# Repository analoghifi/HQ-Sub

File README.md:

# HQ-Sub  
adjustable\* 5th order (**30 dB/oct.**) subsonic filter  
mono module  
\*(13-53Hz / in 2-3Hz steps / 16 steps)  
  
https://web.archive.org/web/20160324051200/http://thel-audioworld.de/module/Filterzone/HQ-Sub.htm

----  

----  

### Frequency Table:  
* 0: 13Hz
* 1: 15Hz
* 2: 18Hz
* 3: 21Hz
* 4: 23Hz
* 5: 26Hz
* 6: 29Hz
* 7: 31Hz
* 8: 34Hz
* 9: 36Hz
* A: 39Hz
* B: 41Hz
* C: 44Hz
* D: 47Hz
* E: 50Hz
* F: 53Hz  

All 5 switches must always be in the same position (!)  
  
----  
  
### A note on the capacitors used in the original design  
The basic problem is:  
to get meaningful (= not too high) resistance values in this 5th order filter design we want to use 1µF capacitors.  
However, 1µF capacitors are generally not available in the KP film/foil version,  
at least not with a 1% tolerance and/or in suitable small dimensions for this small PCB.  
  
regarding C8-C17 in the original design:  
the 1µF MKS capacitors are paralleled with 22nF KP capacitors  
to compensate the very bad (=very high) dissipation factor (tanδ) of the MKS capacitors  
originally equipped with:  
WIMA MKS4    1µF/63V 10%   (Metallized Polyester (PET))     tanδ=8x10<sup>-3</sup> -> <a href="https://github.com/analoghifi/capacitors/blob/main/audio%20and%20filter%20capacitors/docs/datasheets/dont%20use/PET%20MKS/WIMA_MKS_4__EN.pdf">Datasheet</a>  
WIMA FKP2  0,022µF/63V 5%  (film/foil Polypropylene) tanδ=5x10<sup>-4</sup> -> <a href="https://github.com/analoghifi/capacitors/blob/main/audio%20and%20filter%20capacitors/docs/datasheets/kp/WIMA_FKP_2__NEW_ROHS__EN.pdf">Datasheet (ROHS-version)</a>  
(better old FKP2 version "NOS" without ROHS -> <a href ="https://github.com/analoghifi/capacitors/blob/main/audio%20and%20filter%20capacitors/docs/datasheets/kp/WIMA_FKP_2__OLD_nonROHS__EN.pdf">old Datasheet</a>)  
  
another problem is:  
You have to do a lot of component selection work (matching) when using 10% capacitors because:  
Even while it is not so important that the 5 filter capacitors have exactly 1.00 µF,  
they should at least all have the same value (±1%) among each other  
for this kind of 5th order filter arrangement.  
  
#### better alternative (better tolerance & better tanδ):
use good MKP 1% capacitors (with no additional parallel capacitors = omit C9,C11,C13,C15 and C17)  
**for example:**  
Vishay MKP1839 [MKP1839510161] 1µF/160V 1% axial (metallized Polypropylene) tanδ=4x10<sup>-4</sup> -> <a href="https://github.com/analoghifi/capacitors/blob/main/audio%20and%20filter%20capacitors/docs/datasheets/mkp/vishay_mkp1839.pdf">Datasheet</a> -> buy: https://mou.sr/3OpbFIe     
my KiCad PCB (<a href="/hardware/KiCad/original">/hardware/KiCad/original</a>) is prepared for using this big axial capacitors (10.5mm x 26.5mm) in upright position.  
**or another alternative:**  
Dayton Audio "PMPC-1.0 1.0uF 250V Precision Audio Capacitor" (metallized Polypropylene) with 1% tolerance as well   
-> https://www.daytonaudio.com/product/179/pmpc-1-0-1-0uf-250v-precision-audio-capacitor  
-> https://www.soundimports.eu/en/dayton-audio-pmpc-1-0.html  
-> https://www.parts-express.com/Dayton-Audio-PMPC-1.0-1.0uF-250V-Precision-Audio-Capacitor-027-210  
although not knowing the exact<sup>1</sup> tanδ for this type -> will be measured by me soon ...  
  
<sup>1</sup>(the manufacturer's statement: *"Dissipation Factor [tanδ]: Max 0.001 (0.1%) [10x10<sup>-4</sup>] @ 1 KHz"* is only a general worst case statement for the entire series of these capacitors.)
  
----  
### Kicad projects in this repo:  
* [Thel HQ-Sub](https://github.com/analoghifi/HQ-Sub/tree/main/hardware/KiCad/original) | state: initial release v1.01 | like the original, 1-layer, THT

----

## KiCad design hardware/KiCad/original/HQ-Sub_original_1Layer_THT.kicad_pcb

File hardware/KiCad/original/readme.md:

this is not the original Thel PCB but it's very like\* the original with the following exceptions:  
* more massive ground and power supply PCB tracks  
* using the 2mm gold-plated (lathe made) brass solder pins (the same ones used on the more expensive Thel modules)
* swapped positions for C1<->C5 and C2<->C6
* using a special footprint for the 1µF MKS foil caps (C8,C10,C12,C14,C16), so that you can use bigger (better) MKP axial caps in upright position (in this case: omit C9,C11,C13,C15 and C17)
  
\*(same schematic / same board dimensions / same 1-layer\** layout THT / same THT components in the same places on the board)  
\**(strictly speaking, this KiCad PCB is a two-layer PCB with plated-through holes, but you can also (let) produce it as a classic 1-layer PCB with non-plated holes if you wish, since all the tracks are on the bottom side only)  
    
----  
  
### remarks:  
#### U1:  
instead of [MC33078](https://github.com/analoghifi/HQ-Sub/blob/main/docs/components%20datasheet/MC33078_Motorola.pdf) you can use [LME49720](https://github.com/analoghifi/HQ-Sub/blob/main/docs/components%20datasheet/LME49720.pdf) or [LM4562](https://github.com/analoghifi/HQ-Sub/blob/main/docs/components%20datasheet/LM4562.pdf) (both\* Texas Instruments),  
with slightly better technical data regarding noise and THD.  
\*(these two are 100% identical (even regarding their inner guts))  

----  
  
these are KiCad 6.x projects  
see how to get the proper 3D-Models from here: https://github.com/analoghifi/KiCad-3D-Models

----  
  
use kicanvas.org to view this KiCad project in your browser:  
https://kicanvas.org/?github=https%3A%2F%2Fgithub.com%2Fanaloghifi%2FHQ-Sub%2Ftree%2Fmain%2Fhardware%2FKiCad%2Foriginal

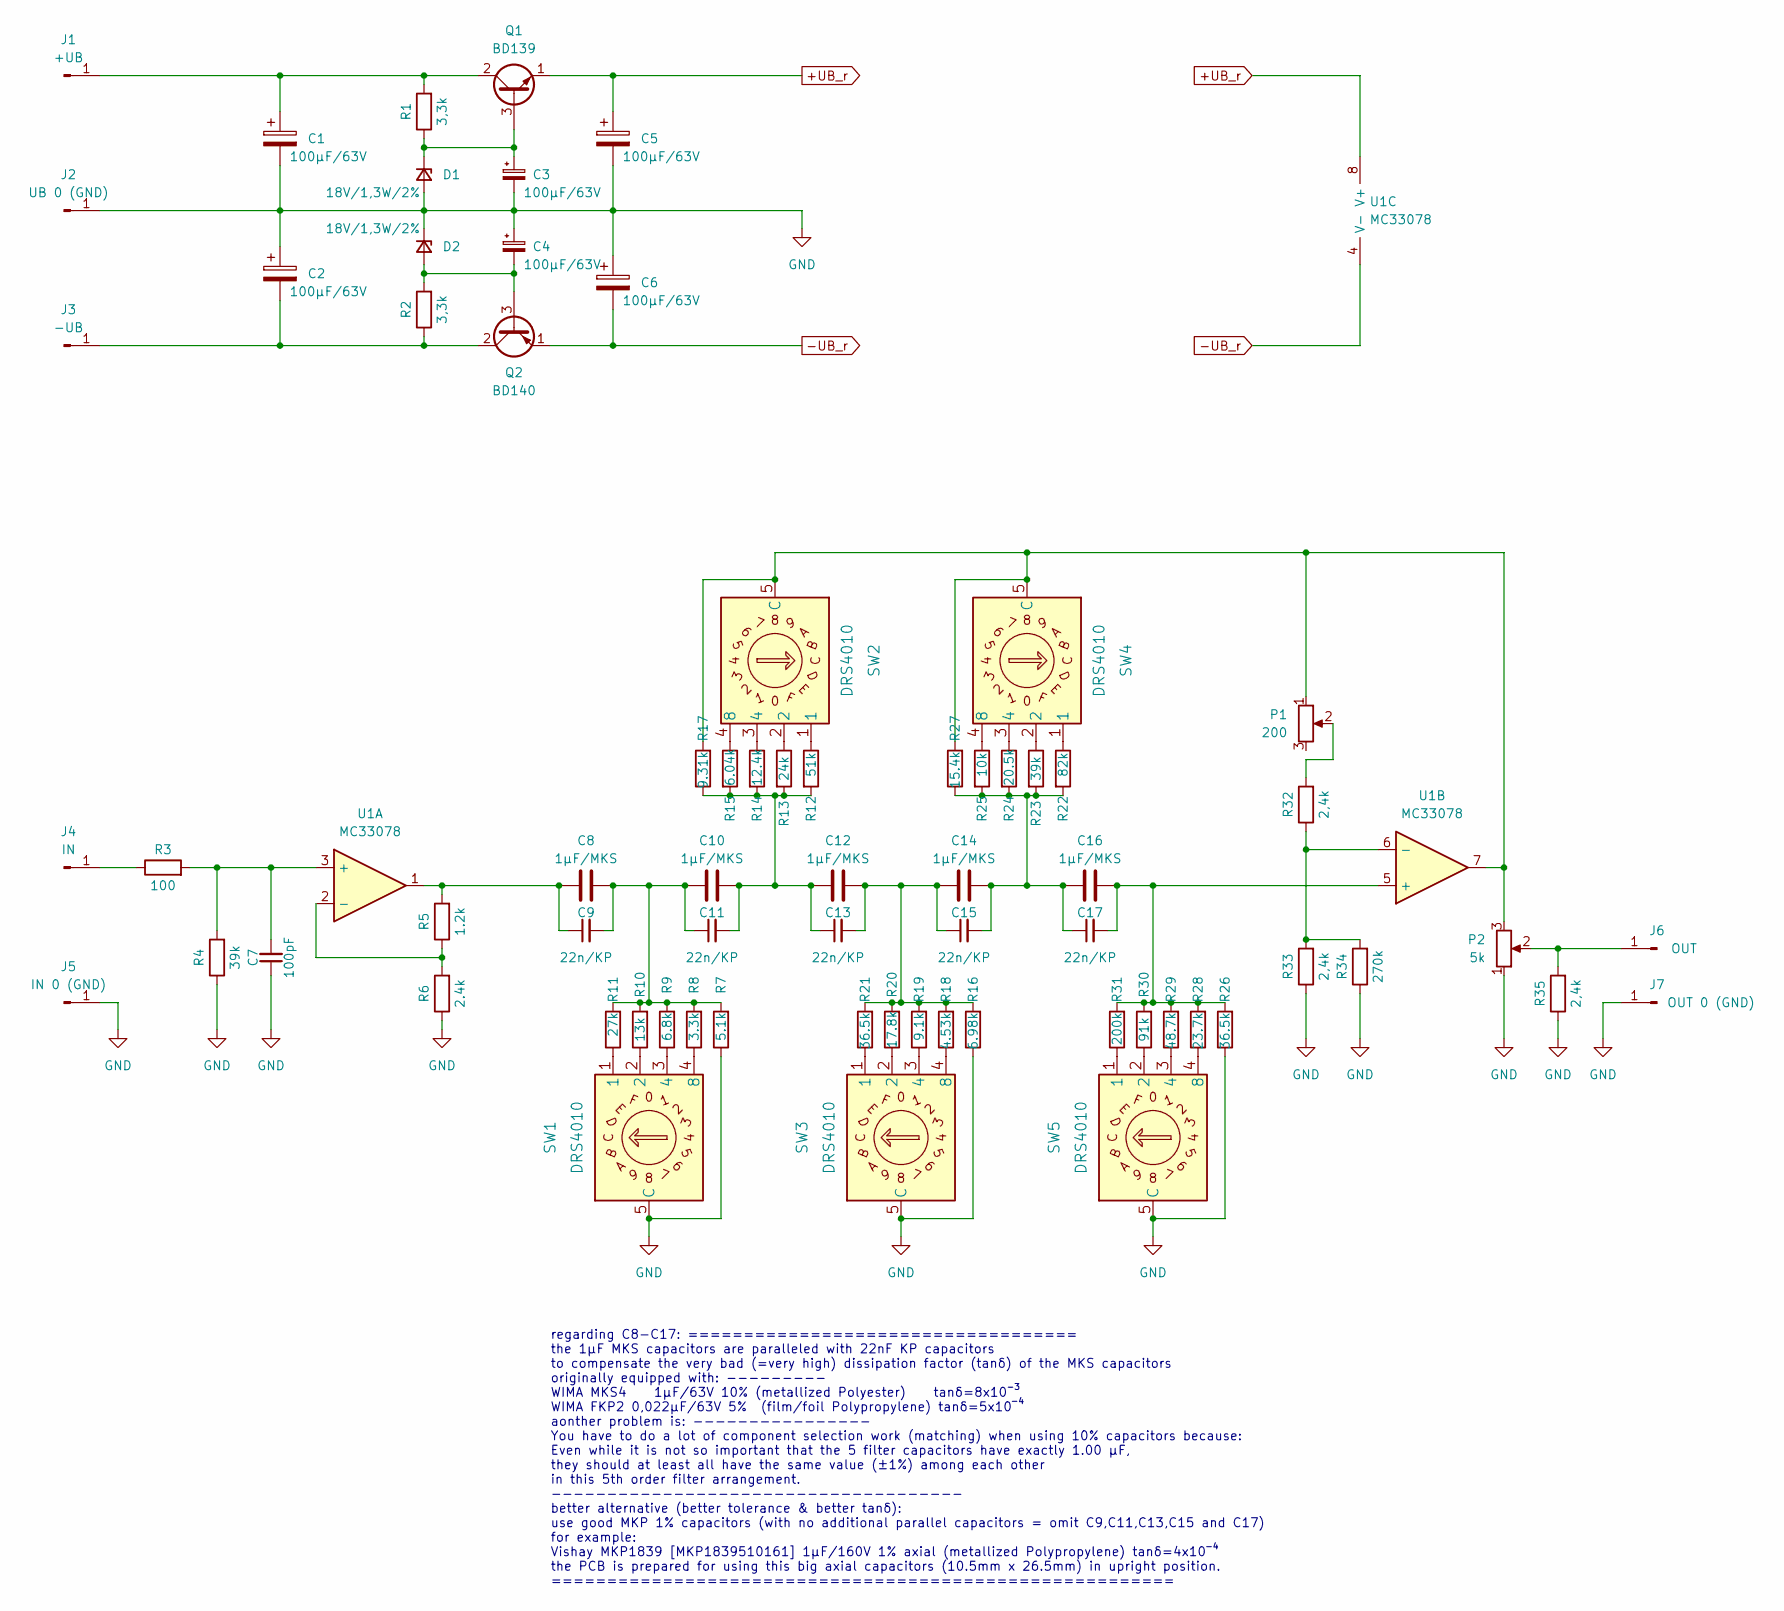
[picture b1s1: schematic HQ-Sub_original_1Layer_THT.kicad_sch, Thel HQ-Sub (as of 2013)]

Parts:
C1, C2, C3, C4, C5, C6: 100µF/63V; CP_Radial_Black_D8.2mm_H12.5mm_P3.50mm_minimal_silk
C7: 100pF; C_Rect_L7.0mm_W2.5mm_P5.00mm
C8, C10, C12, C14, C16: 1µF/MKS; C_Rect_L10.3mm_W5.0mm_P7.50mm_MKS4
C9, C11, C13, C15, C17: 22n/KP; C_Rect_L7.2mm_W7.2mm_P5.00mm_FKS2_FKP2_MKS2_MKP2
D1, D2: 18V/1,3W/2%; D_DO-41_SOD81_P10.16mm_Horizontal_minSilk
J1: +UB; Loet_Pin_D1.5mm_L14.0mm
J2: UB 0 (GND); Loet_Pin_D1.5mm_L14.0mm
J3: -UB; Loet_Pin_D1.5mm_L14.0mm
J4: IN; Loet_Pin_D1.5mm_L14.0mm
J5: IN 0 (GND); Loet_Pin_D1.5mm_L14.0mm
J6: OUT; Loet_Pin_D1.5mm_L14.0mm
J7: OUT 0 (GND); Loet_Pin_D1.5mm_L14.0mm
P1: 200; Potentiometer_Bourns_3386P_Vertical
P2: 5k; Potentiometer_Bourns_3386P_Vertical
Q1: BD139; TO-126-3_Vertical
Q2: BD140; TO-126-3_Vertical
R1, R2: 3,3k; R_Axial_DIN0207_L6.3mm_D2.5mm_P10.16mm_Horizontal_minSilk
R3: 100; R_Axial_DIN0207_L6.3mm_D2.5mm_P10.16mm_Horizontal_minSilk
R4: 39k; R_Axial_Short_L6.3mm_D2.5mm_P9.0mm_Horiz_minSilk
R5: 1.2k; R_Axial_DIN0207_L6.3mm_D2.5mm_P10.16mm_Horizontal_minSilk
R6: 2.4k; R_Axial_DIN0207_L6.3mm_D2.5mm_P10.16mm_Horizontal_minSilk
R7: 5.1k; R_Axial_DIN0207_L6.3mm_D2.5mm_P10.16mm_Horizontal_minSilk
R8: 3.3k; R_Axial_DIN0207_L6.3mm_D2.5mm_P10.16mm_Horizontal_minSilk
R9: 6.8k; R_Axial_DIN0207_L6.3mm_D2.5mm_P10.16mm_Horizontal_minSilk
R10: 13k; R_Axial_DIN0207_L6.3mm_D2.5mm_P10.16mm_Horizontal_minSilk
R11: 27k; R_Axial_DIN0207_L6.3mm_D2.5mm_P10.16mm_Horizontal_minSilk
R12: 51k; R_Axial_DIN0207_L6.3mm_D2.5mm_P10.16mm_Horizontal_minSilk
R13: 24k; R_Axial_DIN0207_L6.3mm_D2.5mm_P10.16mm_Horizontal_minSilk
R14: 12.4k; R_Axial_DIN0207_L6.3mm_D2.5mm_P10.16mm_Horizontal_minSilk
R15: 6.04k; R_Axial_DIN0207_L6.3mm_D2.5mm_P10.16mm_Horizontal_minSilk
R16: 6.98k; R_Axial_DIN0207_L6.3mm_D2.5mm_P10.16mm_Horizontal_minSilk
R17: 9.31k; R_Axial_DIN0207_L6.3mm_D2.5mm_P10.16mm_Horizontal_minSilk
R18: 4.53k; R_Axial_DIN0207_L6.3mm_D2.5mm_P10.16mm_Horizontal_minSilk
R19: 9.1k; R_Axial_DIN0207_L6.3mm_D2.5mm_P10.16mm_Horizontal_minSilk
R20: 17.8k; R_Axial_DIN0207_L6.3mm_D2.5mm_P10.16mm_Horizontal_minSilk
R21, R26: 36.5k; R_Axial_DIN0207_L6.3mm_D2.5mm_P10.16mm_Horizontal_minSilk
R22: 82k; R_Axial_DIN0207_L6.3mm_D2.5mm_P10.16mm_Horizontal_minSilk
R23: 39k; R_Axial_DIN0207_L6.3mm_D2.5mm_P10.16mm_Horizontal_minSilk
R24: 20.5k; R_Axial_DIN0207_L6.3mm_D2.5mm_P10.16mm_Horizontal_minSilk
R25: 10k; R_Axial_DIN0207_L6.3mm_D2.5mm_P10.16mm_Horizontal_minSilk
R27: 15.4k; R_Axial_DIN0207_L6.3mm_D2.5mm_P10.16mm_Horizontal_minSilk
R28: 23.7k; R_Axial_DIN0207_L6.3mm_D2.5mm_P10.16mm_Horizontal_minSilk
R29: 48.7k; R_Axial_DIN0207_L6.3mm_D2.5mm_P10.16mm_Horizontal_minSilk
R30: 91k; R_Axial_DIN0207_L6.3mm_D2.5mm_P10.16mm_Horizontal_minSilk
R31: 200k; R_Axial_DIN0207_L6.3mm_D2.5mm_P10.16mm_Horizontal_minSilk
R32, R33, R35: 2,4k; R_Axial_DIN0207_L6.3mm_D2.5mm_P10.16mm_Horizontal_minSilk
R34: 270k; R_Axial_DIN0207_L6.3mm_D2.5mm_P10.16mm_Horizontal_minSilk
SW1, SW2, SW3, SW4, SW5: DRS4010; DRS_3016_4010
U1: MC33078; DIP-8_W7.62mm

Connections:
+UB_r: C5.1, Q1.1 (E), U1.8 (V+)
-UB_r: C6.2, Q2.1 (E), U1.4 (V-)
GND: C1.2, C2.1, C3.2, C4.1, C5.2, C6.1, C7.1, D1.2 (A), D2.1 (K), J2.1, J5.1, J7.1, P2.1, R4.1, R6.1, R7.1, R16.1, R26.1, R33.1, R34.1, R35.1, SW1.5 (C), SW3.5 (C), SW5.5 (C)
unnamed: C1.1, J1.1, Q1.2 (C), R1.2
unnamed: C2.2, J3.1, Q2.2 (C), R2.1
unnamed: C3.1, D1.1 (K), Q1.3 (B), R1.1
unnamed: C4.2, D2.2 (A), Q2.3 (B), R2.2
unnamed: C7.2, R3.2, R4.2, U1.3 (+)
unnamed: C8.2, C9.1, R5.2, U1.1
unnamed: C8.1, C9.2, C10.2, C11.1, R7.2, R8.2, R9.2, R10.2, R11.2
unnamed: C12.1, C13.2, C14.2, C15.1, R16.2, R18.2, R19.2, R20.2, R21.2
unnamed: C14.1, C15.2, C16.2, C17.1, R22.2, R23.2, R24.2, R25.2, R27.1
unnamed: C16.1, C17.2, R26.2, R28.2, R29.2, R30.2, R31.2, U1.5 (+)
unnamed: J4.1, R3.1
unnamed: J6.1, P2.2, R35.2
unnamed: R5.1, R6.2, U1.2 (-)
unnamed: R8.1, SW1.4 (8)
unnamed: R9.1, SW1.3 (4)
unnamed: R10.1, SW1.2
unnamed: R11.1, SW1.1
unnamed: R12.1, SW2.1
unnamed: C10.1, C11.2, C12.2, C13.1, R12.2, R13.2, R14.2, R15.2, R17.1
unnamed: R13.1, SW2.2
unnamed: R14.1, SW2.3 (4)
unnamed: R15.1, SW2.4 (8)
unnamed: P1.1, P2.3, R17.2, R27.2, SW2.5 (C), SW4.5 (C), U1.7
unnamed: R18.1, SW3.4 (8)
unnamed: R19.1, SW3.3 (4)
unnamed: R20.1, SW3.2
unnamed: R21.1, SW3.1
unnamed: R22.1, SW4.1
unnamed: R23.1, SW4.2
unnamed: R24.1, SW4.3 (4)
unnamed: R25.1, SW4.4 (8)
unnamed: R28.1, SW5.4 (8)
unnamed: R29.1, SW5.3 (4)
unnamed: R30.1, SW5.2
unnamed: R31.1, SW5.1
unnamed: R32.1, R33.2, R34.2, U1.6 (-)
unnamed: P1.2, R32.2

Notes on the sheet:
regarding C8-C17: =================================== the 1µF MKS capacitors are paralleled with 22nF KP capacitors to compensate the very bad (=very high) dissipation factor (tanδ) of the MKS capacitors originally equipped with: --------- WIMA MKS4 1µF/63V 10% (metallized Polyester) tanδ=8x10 WIMA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

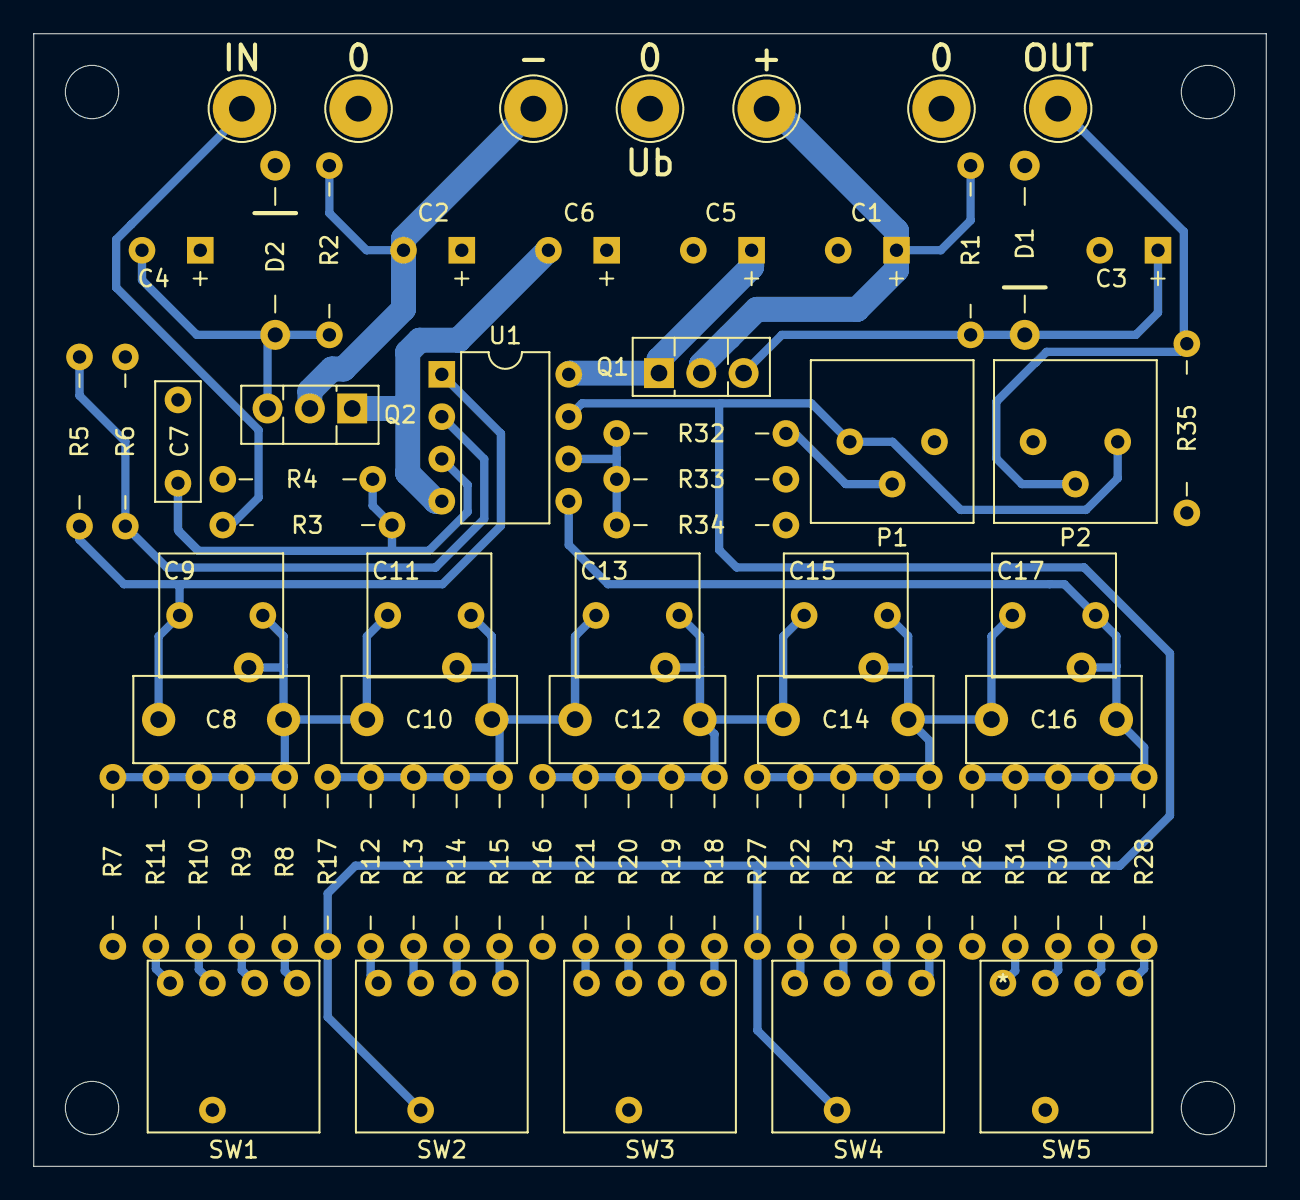
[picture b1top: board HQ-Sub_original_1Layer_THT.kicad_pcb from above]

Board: 2 copper layers, 74.0 x 68.0 mm, 71 parts (0 on the bottom side), 40 nets.
